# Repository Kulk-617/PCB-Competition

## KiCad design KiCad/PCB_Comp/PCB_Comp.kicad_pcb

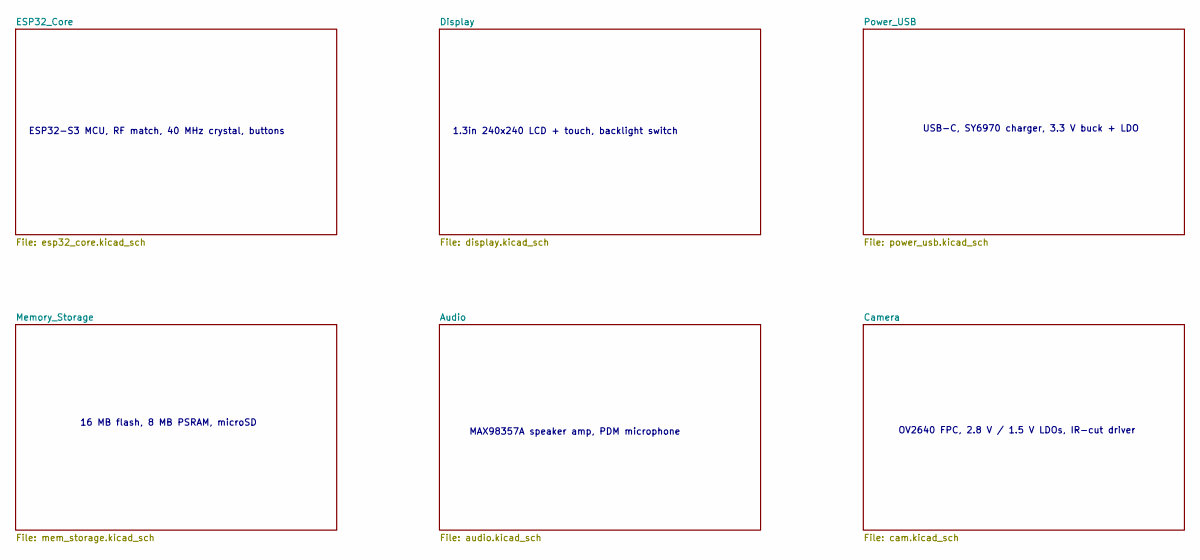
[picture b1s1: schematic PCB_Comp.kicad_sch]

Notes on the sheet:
ESP32-S3 MCU, RF match, 40 MHz crystal, buttons
16 MB flash, 8 MB PSRAM, microSD
OV2640 FPC, 2.8 V / 1.5 V LDOs, IR-cut driver
1.3in 240x240 LCD + touch, backlight switch
USB-C, SY6970 charger, 3.3 V buck + LDO
MAX98357A speaker amp, PDM microphone

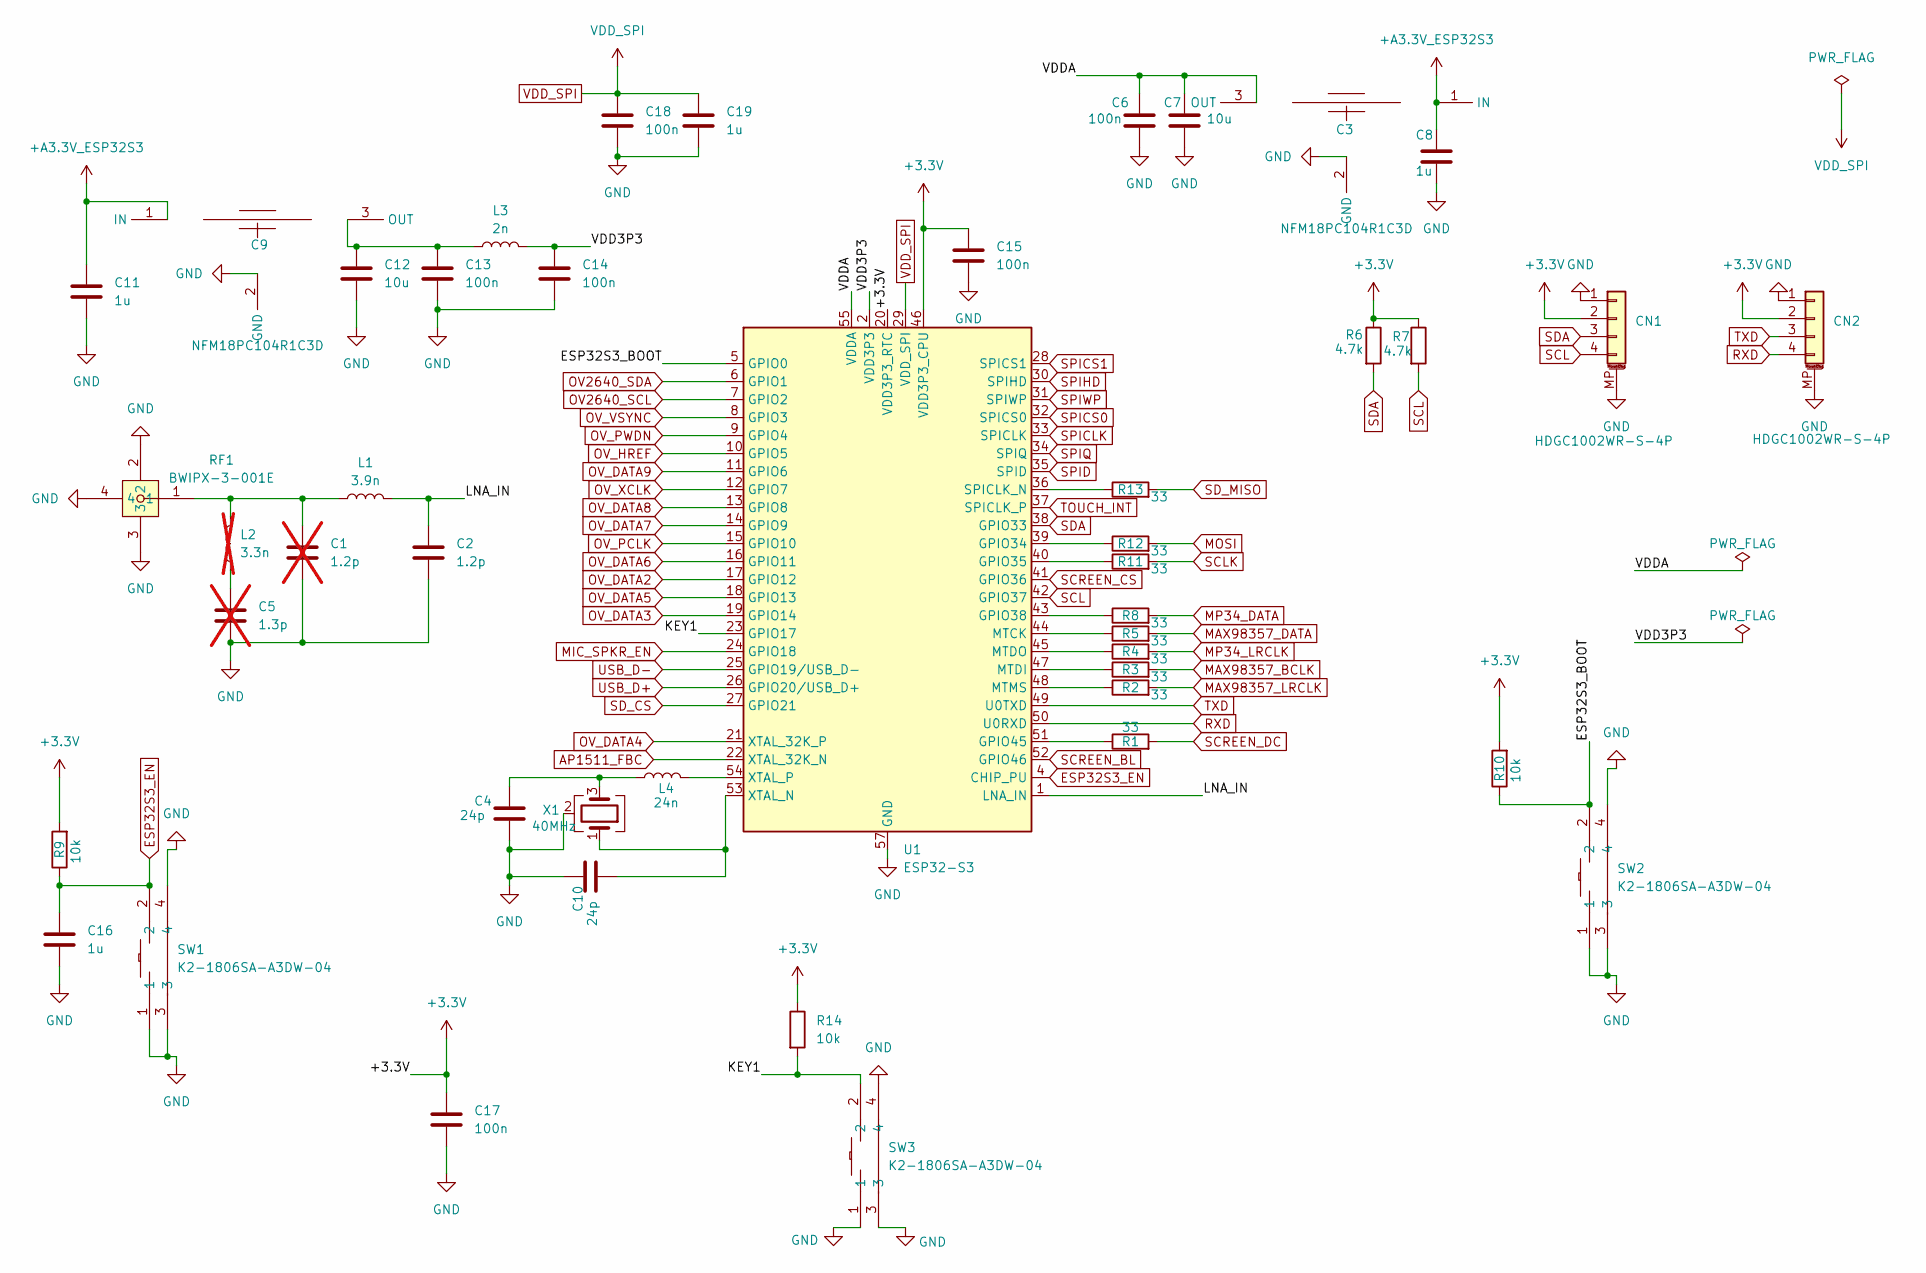
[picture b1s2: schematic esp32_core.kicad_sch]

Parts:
C1: 1.2p; C_0402_1005Metric; not fitted
C2: 1.2p; C_0402_1005Metric
C3, C9: NFM18PC104R1C3D; FILTER-SMD_3P-L1.6-W0.8-L_NFM18CC223R1C3D; MPN NFM18PC104R1C3D; LCSC Part C111493
C4, C10: 24p; C_0402_1005Metric
C5: 1.3p; C_0402_1005Metric; not fitted
C6, C13, C14, C15, C17, C18: 100n; C_0402_1005Metric
C7, C12: 10u; C_0603_1608Metric
C8, C11, C16, C19: 1u; C_0402_1005Metric
CN1, CN2: HDGC1002WR-S-4P; JST_SH_SM04B-SRSS-TB_1x04-1MP_P1.00mm_Horizontal
L1: 3.9n; L_0402_1005Metric
L2: 3.3n; L_0402_1005Metric; not fitted
L3: 2n; L_0402_1005Metric
L4: 24n; L_0402_1005Metric
R1, R2, R3, R4, R5, R8, R11, R12, R13: 33; R_0402_1005Metric
R6, R7: 4.7k; R_0402_1005Metric
R9, R10, R14: 10k; R_0402_1005Metric
RF1: BWIPX-3-001E; IPEX-SMD_BWIPX-3-001E-1; MPN BWIPX-3-001E; LCSC Part C784400
SW1, SW2, SW3: K2-1806SA-A3DW-04; KEY-SMD_K2-1806SA-AXXW-XX; MPN K2-1806SA-A3DW-04; LCSC Part C2690015
U1: ESP32-S3; QFN-56-1EP_7x7mm_P0.4mm_EP4x4mm
X1: 40MHz; Crystal_SMD_3225-4Pin_3.2x2.5mm

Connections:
+3.3V: C15.1, C17.1, CN1.2, CN2.2, R6.1, R7.1, R9.2, R10.2, R14.1, U1.20 (VDD3P3_RTC), U1.46 (VDD3P3_CPU); also elsewhere on the board
+A3.3V_ESP32S3: C3.1 (IN), C8.1, C9.1 (IN), C11.1; also elsewhere on the board
/ESP32_Core/ESP32S3_BOOT: R10.1, SW2.2, U1.5 (GPIO0)
/ESP32_Core/KEY1: R14.2, SW3.2, U1.23 (GPIO17)
/ESP32_Core/LNA_IN: C2.1, L1.2, U1.1 (LNA_IN)
/ESP32_Core/VDD3P3: C14.1, L3.2, U1.2 (VDD3P3), U1.3 (VDD3P3)
/ESP32_Core/VDDA: C3.3 (OUT), C6.1, C7.1, U1.55 (VDDA), U1.56 (VDDA)
AP1511_FBC: U1.22 (XTAL_32K_N); also elsewhere on the board
ESP32S3_EN: C16.1, R9.1, SW1.2, U1.4 (CHIP_PU)
GND: C1.2, C2.2, C3.2 (GND), C4.2, C5.2, C6.2, C7.2, C8.2, C9.2 (GND), C10.1, C11.2, C12.2, C13.2, C14.2, C15.2, C16.2, C17.2, C18.2, C19.2, CN1.1, CN1.MP (MountPin), CN2.1, CN2.MP (MountPin), RF1.2, RF1.3, RF1.4, SW1.1, SW1.3, SW1.4, SW2.1, SW2.3, SW2.4, SW3.1, SW3.3, SW3.4, U1.57 (GND), X1.2 (G), X1.4 (G); also elsewhere on the board
MAX98357_BCLK: R3.2; also elsewhere on the board
MAX98357_DATA: R5.2; also elsewhere on the board
MAX98357_LRCLK: R2.2; also elsewhere on the board
MIC_SPKR_EN: U1.24 (GPIO18); also elsewhere on the board
MOSI: R12.2; also elsewhere on the board
MP34_DATA: R8.2; also elsewhere on the board
MP34_LRCLK: R4.2; also elsewhere on the board
unnamed: C1.1, L1.1, L2.2, RF1.1
unnamed: C4.1, L4.1, X1.3
unnamed: C5.1, L2.1
unnamed: C9.3 (OUT), C12.1, C13.1, L3.1
unnamed: R12.1, U1.39 (GPIO34)
unnamed: R11.1, U1.40 (GPIO35)
unnamed: R8.1, U1.43 (GPIO38)
unnamed: R1.1, U1.51 (GPIO45)
unnamed: R5.1, U1.44 (MTCK)
unnamed: R3.1, U1.47 (MTDI)
unnamed: R4.1, U1.45 (MTDO)
unnamed: R2.1, U1.48 (MTMS)
unnamed: R13.1, U1.36 (SPICLK_N)
unnamed: C10.2, U1.53 (XTAL_N), X1.1
unnamed: L4.2, U1.54 (XTAL_P)
OV2640_SCL: U1.7 (GPIO2); also elsewhere on the board
OV2640_SDA: U1.6 (GPIO1); also elsewhere on the board
OV_DATA2: U1.17 (GPIO12); also elsewhere on the board
OV_DATA3: U1.19 (GPIO14); also elsewhere on the board
OV_DATA4: U1.21 (XTAL_32K_P); also elsewhere on the board
OV_DATA5: U1.18 (GPIO13); also elsewhere on the board
OV_DATA6: U1.16 (GPIO11); also elsewhere on the board
OV_DATA7: U1.14 (GPIO9); also elsewhere on the board
OV_DATA8: U1.13 (GPIO8); also elsewhere on the board
OV_DATA9: U1.11 (GPIO6); also elsewhere on the board
OV_HREF: U1.10 (GPIO5); also elsewhere on the board
OV_PCLK: U1.15 (GPIO10); also elsewhere on the board
OV_PWDN: U1.9 (GPIO4); also elsewhere on the board
OV_VSYNC: U1.8 (GPIO3); also elsewhere on the board
OV_XCLK: U1.12 (GPIO7); also elsewhere on the board
RXD: CN2.4, U1.50 (U0RXD)
SCL: CN1.4, R7.2, U1.42 (GPIO37); also elsewhere on the board
SCLK: R11.2; also elsewhere on the board
SCREEN_BL: U1.52 (GPIO46); also elsewhere on the board
SCREEN_CS: U1.41 (GPIO36); also elsewhere on the board
SCREEN_DC: R1.2; also elsewhere on the board
SDA: CN1.3, R6.2, U1.38 (GPIO33); also elsewhere on the board
SD_CS: U1.27 (GPIO21); also elsewhere on the board
SD_MISO: R13.2; also elsewhere on the board
SPICLK: U1.33 (SPICLK); also elsewhere on the board
SPICS0: U1.32 (SPICS0); also elsewhere on the board
SPICS1: U1.28 (SPICS1); also elsewhere on the board
SPID: U1.35 (SPID); also elsewhere on the board
SPIHD: U1.30 (SPIHD); also elsewhere on the board
SPIQ: U1.34 (SPIQ); also elsewhere on the board
SPIWP: U1.31 (SPIWP); also elsewhere on the board
TOUCH_INT: U1.37 (SPICLK_P); also elsewhere on the board
TXD: CN2.3, U1.49 (U0TXD)
USB_D+: U1.26 (GPIO20/USB_D+); also elsewhere on the board
USB_D-: U1.25 (GPIO19/USB_D-); also elsewhere on the board
VDD_SPI: C18.1, C19.1, U1.29 (VDD_SPI); also elsewhere on the board

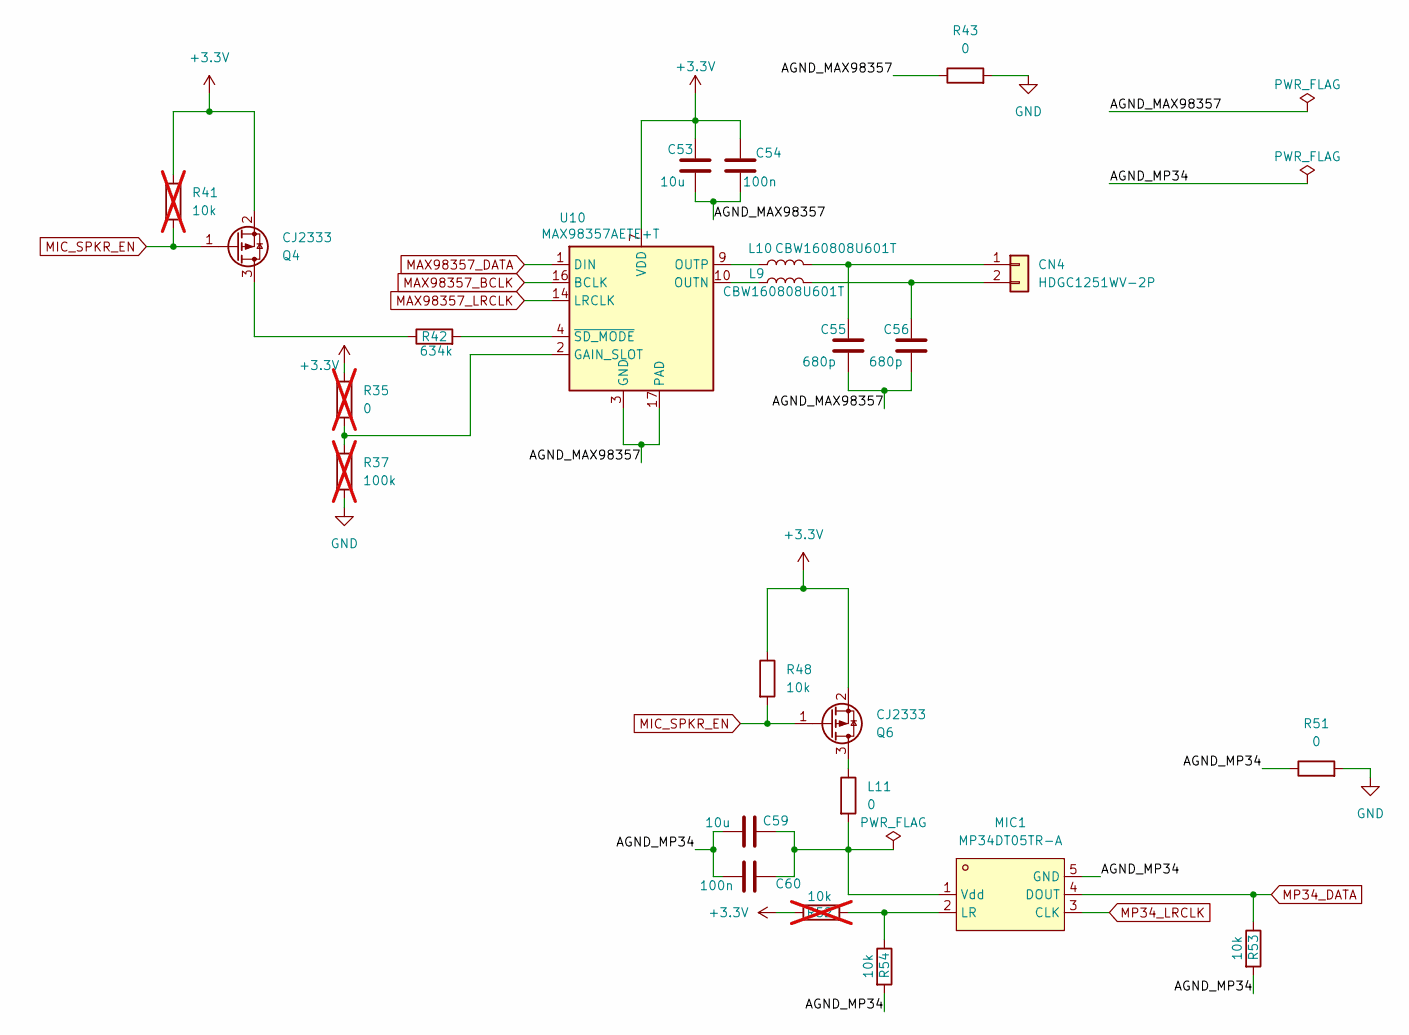
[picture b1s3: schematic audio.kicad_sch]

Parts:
C53, C59: 10u; C_0603_1608Metric
C54, C60: 100n; C_0402_1005Metric
C55, C56: 680p; C_0402_1005Metric
CN4: HDGC1251WV-2P; CONN-TH_2P-P1.25_HDGC1251WV-2P
L9, L10: CBW160808U601T; L_0603_1608Metric
L11: 0; R_0402_1005Metric
MIC1: MP34DT05TR-A; MIC-SMD_5P-L3.0-W4.0-P0.85-BL; MPN MP34DT05TR-A; LCSC Part C2688664
Q4, Q6: CJ2333; SOT-23
R35: 0; R_0402_1005Metric; not fitted
R37: 100k; R_0402_1005Metric; not fitted
R41, R52: 10k; R_0402_1005Metric; not fitted
R42: 634k; R_0402_1005Metric
R43, R51: 0; R_0603_1608Metric
R48, R53, R54: 10k; R_0402_1005Metric
U10: MAX98357AETE+T; TQFN-16-1EP_3x3mm_P0.5mm_EP1.23x1.23mm

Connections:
+3.3V: C53.1, C54.1, Q4.2 (S), Q6.2 (S), R35.1, R41.1, R48.1, R52.1, U10.7 (VDD), U10.8 (VDD); also elsewhere on the board
/Audio/AGND_MAX98357: C53.2, C54.2, C55.2, C56.2, R43.1, U10.3 (GND), U10.11 (GND), U10.15 (GND), U10.17 (PAD)
/Audio/AGND_MP34: C59.2, C60.2, MIC1.5 (GND), R51.1, R53.2, R54.2
GND: R37.2, R43.2, R51.2; also elsewhere on the board
MAX98357_BCLK: U10.16 (BCLK); also elsewhere on the board
MAX98357_DATA: U10.1 (DIN); also elsewhere on the board
MAX98357_LRCLK: U10.14 (LRCLK); also elsewhere on the board
MIC_SPKR_EN: Q4.1 (G), Q6.1 (G), R41.2, R48.2; also elsewhere on the board
MP34_DATA: MIC1.4 (DOUT), R53.1; also elsewhere on the board
MP34_LRCLK: MIC1.3 (CLK); also elsewhere on the board
unnamed: C55.1, CN4.1, L10.2
unnamed: C56.1, CN4.2, L9.2
unnamed: MIC1.2 (LR), R52.2, R54.1
unnamed: C59.1, C60.1, L11.2, MIC1.1 (Vdd)
unnamed: Q4.3 (D), R42.1
unnamed: L11.1, Q6.3 (D)
unnamed: R35.2, R37.1, U10.2 (GAIN_SLOT)
unnamed: L9.1, U10.10 (OUTN)
unnamed: L10.1, U10.9 (OUTP)
unnamed: R42.2, U10.4 (~SD_MODE)

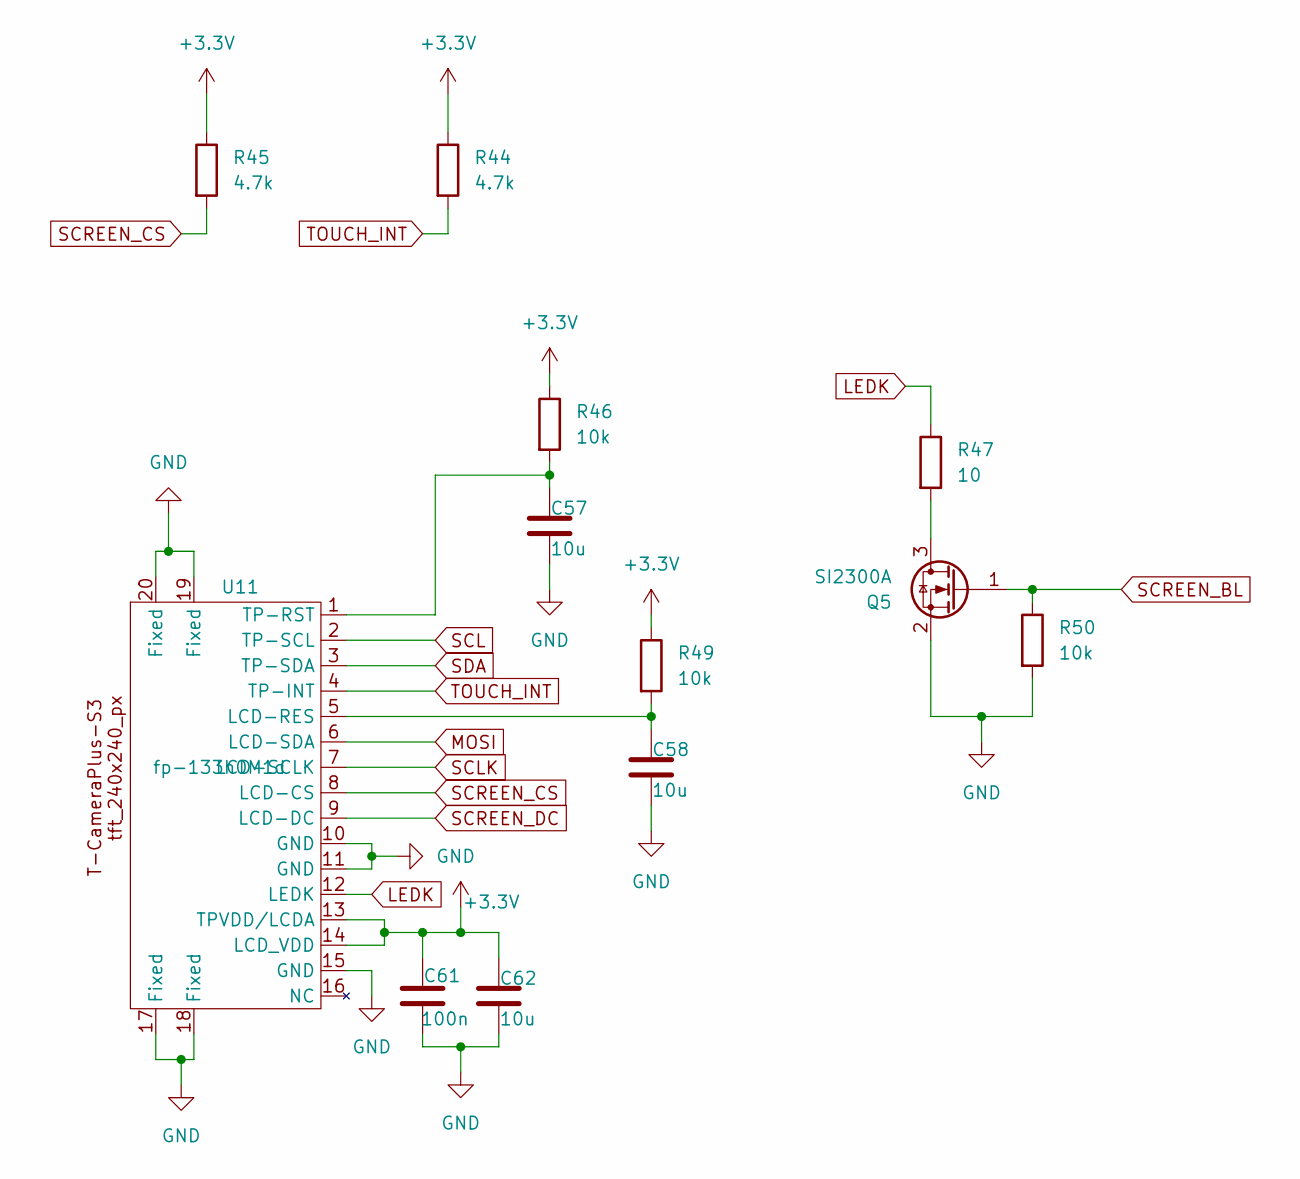
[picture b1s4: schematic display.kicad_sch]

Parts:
C57, C58, C62: 10u; C_0603_1608Metric
C61: 100n; C_0402_1005Metric
Q5: SI2300A; SOT-23
R44, R45: 4.7k; R_0402_1005Metric
R46, R49, R50: 10k; R_0402_1005Metric
R47: 10; R_0402_1005Metric
U11: fp-133h0M1d; LCD_FPC-16P_P0.5mm_FH12-16S

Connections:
+3.3V: C61.1, C62.1, R44.1, R45.1, R46.1, R49.1, U11.13 (TPVDD/LCDA), U11.14 (LCD_VDD); also elsewhere on the board
GND: C57.2, C58.2, C61.2, C62.2, Q5.2 (S), R50.2, U11.10 (GND), U11.11 (GND), U11.15 (GND), U11.17 (Fixed), U11.18 (Fixed), U11.19 (Fixed), U11.20 (Fixed); also elsewhere on the board
LEDK: R47.1, U11.12 (LEDK)
MOSI: U11.6 (LCD-SDA); also elsewhere on the board
unnamed: Q5.3 (D), R47.2
unnamed: C58.1, R49.2, U11.5 (LCD-RES)
unnamed: C57.1, R46.2, U11.1 (TP-RST)
SCL: U11.2 (TP-SCL); also elsewhere on the board
SCLK: U11.7 (LCD-SCLK); also elsewhere on the board
SCREEN_BL: Q5.1 (G), R50.1; also elsewhere on the board
SCREEN_CS: R45.2, U11.8 (LCD-CS); also elsewhere on the board
SCREEN_DC: U11.9 (LCD-DC); also elsewhere on the board
SDA: U11.3 (TP-SDA); also elsewhere on the board
TOUCH_INT: R44.2, U11.4 (TP-INT); also elsewhere on the board

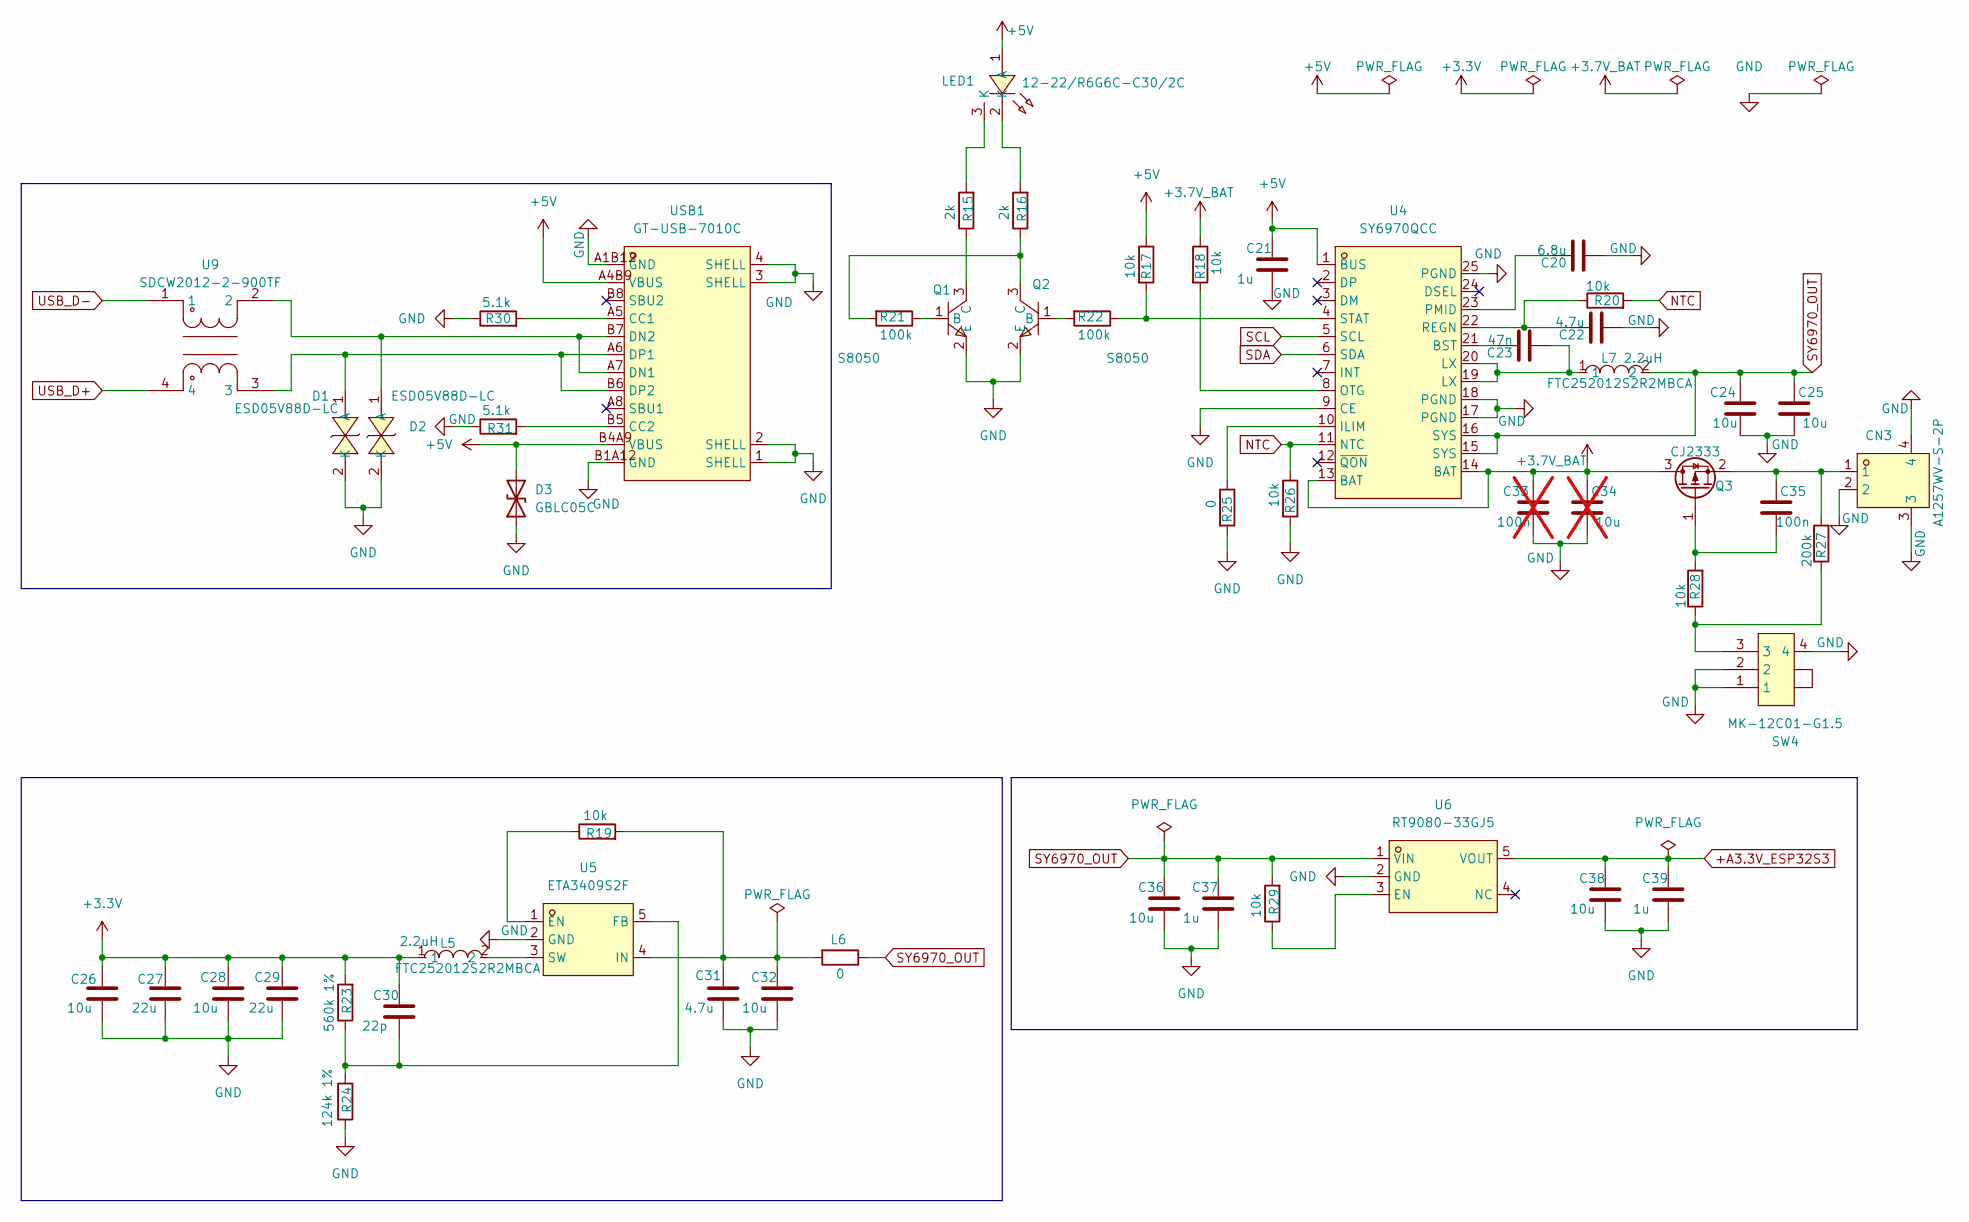
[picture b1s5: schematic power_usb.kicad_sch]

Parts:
C20: 6.8u; C_0603_1608Metric
C21, C37, C39: 1u; C_0402_1005Metric
C22, C31: 4.7u; C_0603_1608Metric
C23: 47n; C_0402_1005Metric
C24, C25, C26, C28, C32, C36, C38: 10u; C_0603_1608Metric
C27, C29: 22u; C_0805_2012Metric
C30: 22p; C_0402_1005Metric
C33: 100n; C_0402_1005Metric; not fitted
C34: 10u; C_0603_1608Metric; not fitted
C35: 100n; C_0402_1005Metric
CN3: A1257WV-S-2P; CONN-SMD_A1257WV-S-2P; MPN A1257WV-S-2P-LCP; LCSC Part C225118
D1, D2: ESD05V88D-LC; DFN1006-2L-BI; MPN ESD05V88D-LC; LCSC Part C5139330
D3: GBLC05C; D_SOD-323
L5, L7: 2.2uH; IND-SMD_L2.5-W2.0_MHCHL2520; MPN FTC252012S2R2MBCA; LCSC Part C5832372
L6: 0; R_0805_2012Metric
LED1: 12-22/R6G6C-C30/2C; LED-SMD_R6G6C-C30; MPN 12-22/R6G6C-C30/2C; LCSC Part C970147
Q1, Q2: S8050; SOT-23-3_L2.9-W1.3-P1.90-LS2.4-BR; MPN S8050; LCSC Part C2891804
Q3: CJ2333; SOT-23
R15, R16: 2k; R_0402_1005Metric
R17, R18, R19, R20, R26, R28, R29: 10k; R_0402_1005Metric
R21, R22: 100k; R_0402_1005Metric
R23: 560k 1%; R_0402_1005Metric
R24: 124k 1%; R_0402_1005Metric
R25: 0; R_0402_1005Metric
R27: 200k; R_0402_1005Metric
R30, R31: 5.1k; R_0402_1005Metric
SW4: MK-12C01-G1.5; SW-SMD_DEALON_MK-12C01-G1.5; MPN MK-12C01-G1.5; LCSC Part C2904924
U4: SY6970QCC; QFN-24_L4.0-W4.0-P0.50-TL-EP2.7; MPN SY6970QCC; LCSC Part C5357542
U5: ETA3409S2F; SOT-23-5_L2.9-W1.6-P0.95-LS2.8-BL; MPN ETA3409S2F; LCSC Part C7465553
U6: RT9080-33GJ5; TSOT-23-5_L2.9-W1.6-P0.95-LS2.8-BL; MPN RT9080-33GJ5; LCSC Part C841192
U9: SDCW2012-2-900TF; FILTER-SMD_4P-L2.0-W1.3-BL_DLW21; MPN SDCW2012-2-900TF; LCSC Part C54888
USB1: GT-USB-7010C; USB-C-SMD_GT-USB-7010C; MPN GT-USB-7010C; LCSC Part C2843967

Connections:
+3.3V: C26.1, C27.1, C28.1, C29.1, C30.1, L5.1, R23.2; also elsewhere on the board
+3.7V_BAT: C33.2, C34.2, Q3.3 (D), R18.1, U4.13 (BAT), U4.14 (BAT)
+5V: C21.1, D3.2 (A2), LED1.1 (A), R17.1, U4.1 (BUS), USB1.A4B9 (VBUS), USB1.B4A9 (VBUS)
+A3.3V_ESP32S3: C38.1, C39.1, U6.5 (VOUT); also elsewhere on the board
GND: C20.2, C21.2, C22.2, C24.1, C25.1, C26.2, C27.2, C28.2, C29.2, C31.2, C32.2, C33.1, C34.1, C36.2, C37.2, C38.2, C39.2, CN3.2, CN3.3, CN3.4, D1.2 (K), D2.2 (K), D3.1 (A1), Q1.2 (E), Q2.2 (E), R24.1, R25.2, R26.2, R30.1, R31.1, SW4.1, SW4.2, SW4.4, U4.9 (CE), U4.17 (PGND), U4.18 (PGND), U4.25 (PGND), U5.2 (GND), U6.2 (GND), USB1.1 (SHELL), USB1.2 (SHELL), USB1.3 (SHELL), USB1.4 (SHELL), USB1.A1B12 (GND), USB1.B1A12 (GND); also elsewhere on the board
NTC: R20.2, R26.1, U4.11 (NTC)
unnamed: C23.2, L7.1, U4.19 (LX), U4.20 (LX)
unnamed: D1.1 (A), U9.3, USB1.A6 (DP1), USB1.B6 (DP2)
unnamed: D2.1 (A), U9.2, USB1.A7 (DN1), USB1.B7 (DN2)
unnamed: LED1.2 (K), R16.2
unnamed: LED1.3 (K), R15.2
unnamed: Q1.1 (B), R21.1
unnamed: Q1.3 (C), R15.1
unnamed: Q2.1 (B), R22.2
unnamed: Q2.3 (C), R16.1, R21.2
unnamed: C35.1, Q3.1 (G), R28.2
unnamed: C35.2, CN3.1, Q3.2 (S), R27.2
unnamed: R27.1, R28.1, SW4.3
unnamed: C23.1, U4.21 (BST)
unnamed: R25.1, U4.10 (ILIM)
unnamed: R18.2, U4.8 (OTG)
unnamed: C20.1, U4.23 (PMID)
unnamed: C22.1, R20.1, U4.22 (REGN)
unnamed: R17.2, R22.1, U4.4 (STAT)
unnamed: R19.1, U5.1 (EN)
unnamed: C30.2, R23.1, R24.2, U5.5 (FB)
unnamed: C31.1, C32.1, L6.2, R19.2, U5.4 (IN)
unnamed: L5.2, U5.3 (SW)
unnamed: R29.1, U6.3 (EN)
unnamed: R30.2, USB1.A5 (CC1)
unnamed: R31.2, USB1.B5 (CC2)
SCL: U4.5 (SCL); also elsewhere on the board
SDA: U4.6 (SDA); also elsewhere on the board
SY6970_OUT: C24.2, C25.2, C36.1, C37.1, L6.1, L7.2, R29.2, U4.15 (SYS), U4.16 (SYS), U6.1 (VIN); also elsewhere on the board
USB_D+: U9.4; also elsewhere on the board
USB_D-: U9.1; also elsewhere on the board

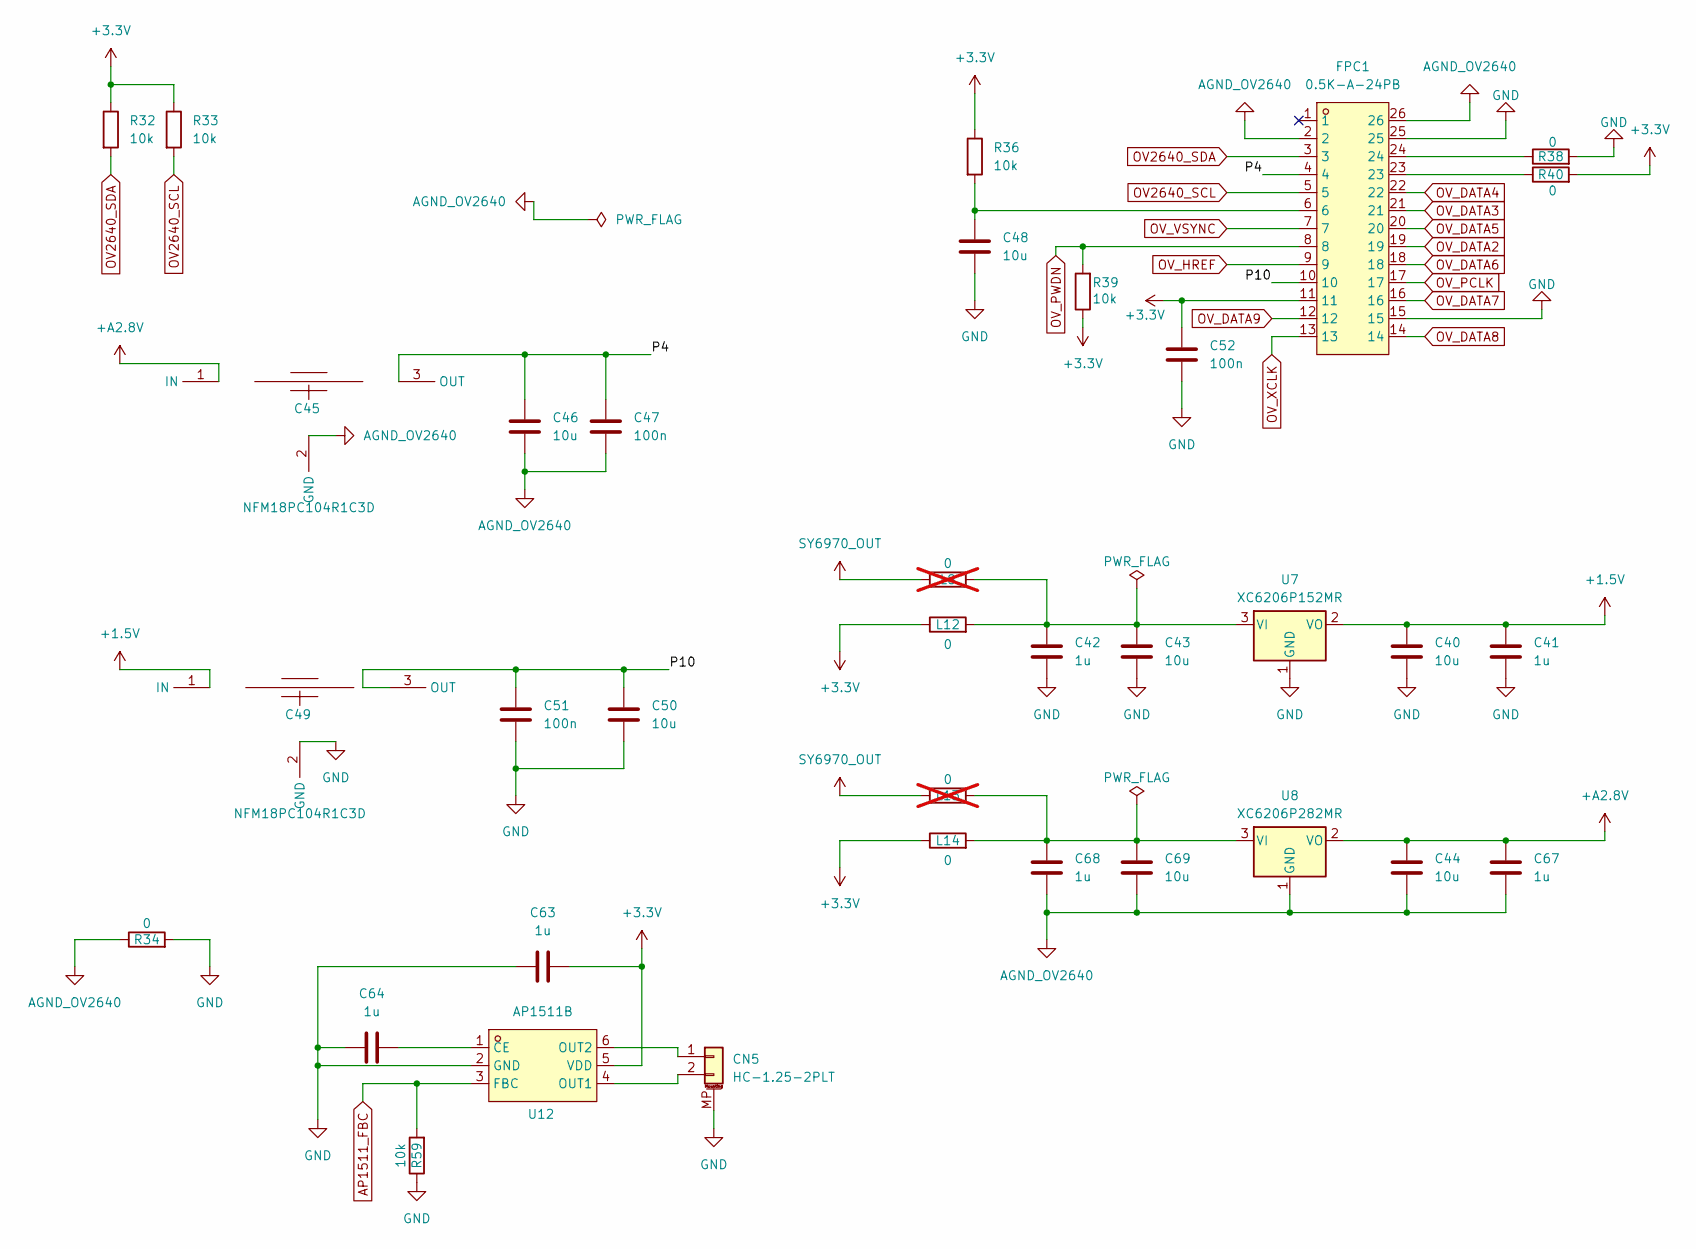
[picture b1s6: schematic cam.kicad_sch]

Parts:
C40, C43, C44, C46, C48, C50, C69: 10u; C_0603_1608Metric
C41, C42, C63, C64, C67, C68: 1u; C_0402_1005Metric
C45, C49: NFM18PC104R1C3D; FILTER-SMD_3P-L1.6-W0.8-L_NFM18CC223R1C3D; MPN NFM18PC104R1C3D; LCSC Part C111493
C47, C51, C52: 100n; C_0402_1005Metric
CN5: HC-1.25-2PLT; Molex_PicoBlade_53261-0271_1x02-1MP_P1.25mm_Horizontal
FPC1: 0.5K-A-24PB; CONN-SMD_0.5K-A-24PB; MPN 0.5K-A-24PB; LCSC Part C2914148
L8, L13: 0; R_0402_1005Metric; not fitted
L12, L14: 0; R_0402_1005Metric
R32, R33, R36, R39, R59: 10k; R_0402_1005Metric
R34: 0; R_0603_1608Metric
R38, R40: 0; R_0402_1005Metric
U7: XC6206P152MR; SOT-23-3
U8: XC6206P282MR; SOT-23-3
U12: AP1511B; SOT-23-6_L2.9-W1.6-P0.95-LS2.9-BL; MPN AP1511B; LCSC Part C22358680

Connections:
+1.5V: C40.1, C41.1, C49.1 (IN), U7.2 (VO)
+3.3V: C52.1, C63.2, FPC1.11, L12.1, L14.1, R32.1, R33.1, R36.1, R39.1, R40.2, U12.5 (VDD); also elsewhere on the board
+A2.8V: C44.1, C45.1 (IN), C67.1, U8.2 (VO); also elsewhere on the board
/Camera/P4: C45.3 (OUT), C46.1, C47.1, FPC1.4
/Camera/P10: C49.3 (OUT), C50.1, C51.1, FPC1.10
AGND_OV2640: C44.2, C45.2 (GND), C46.2, C47.2, C67.2, C68.2, C69.2, FPC1.2, FPC1.26, R34.1, U8.1 (GND); also elsewhere on the board
AP1511_FBC: R59.2, U12.3 (FBC); also elsewhere on the board
GND: C40.2, C41.2, C42.2, C43.2, C48.2, C49.2 (GND), C50.2, C51.2, C52.2, C63.1, C64.1, CN5.MP (MountPin), FPC1.15, FPC1.25, R34.2, R38.2, R59.1, U7.1 (GND), U12.2 (GND); also elsewhere on the board
unnamed: C48.1, FPC1.6, R36.2
unnamed: CN5.1, U12.6 (OUT2)
unnamed: CN5.2, U12.4 (OUT1)
unnamed: FPC1.23, R40.1
unnamed: FPC1.24, R38.1
unnamed: C42.1, C43.1, L8.2, L12.2, U7.3 (VI)
unnamed 79: C68.1, C69.1, L13.2, L14.2, U8.3 (VI); also elsewhere on the board
unnamed: C64.2, U12.1 (CE)
OV2640_SCL: FPC1.5, R33.2; also elsewhere on the board
OV2640_SDA: FPC1.3, R32.2; also elsewhere on the board
OV_DATA2: FPC1.19; also elsewhere on the board
OV_DATA3: FPC1.21; also elsewhere on the board
OV_DATA4: FPC1.22; also elsewhere on the board
OV_DATA5: FPC1.20; also elsewhere on the board
OV_DATA6: FPC1.18; also elsewhere on the board
OV_DATA7: FPC1.16; also elsewhere on the board
OV_DATA8: FPC1.14; also elsewhere on the board
OV_DATA9: FPC1.12; also elsewhere on the board
OV_HREF: FPC1.9; also elsewhere on the board
OV_PCLK: FPC1.17; also elsewhere on the board
OV_PWDN: FPC1.8, R39.2; also elsewhere on the board
OV_VSYNC: FPC1.7; also elsewhere on the board
OV_XCLK: FPC1.13; also elsewhere on the board
SY6970_OUT: L8.1, L13.1; also elsewhere on the board

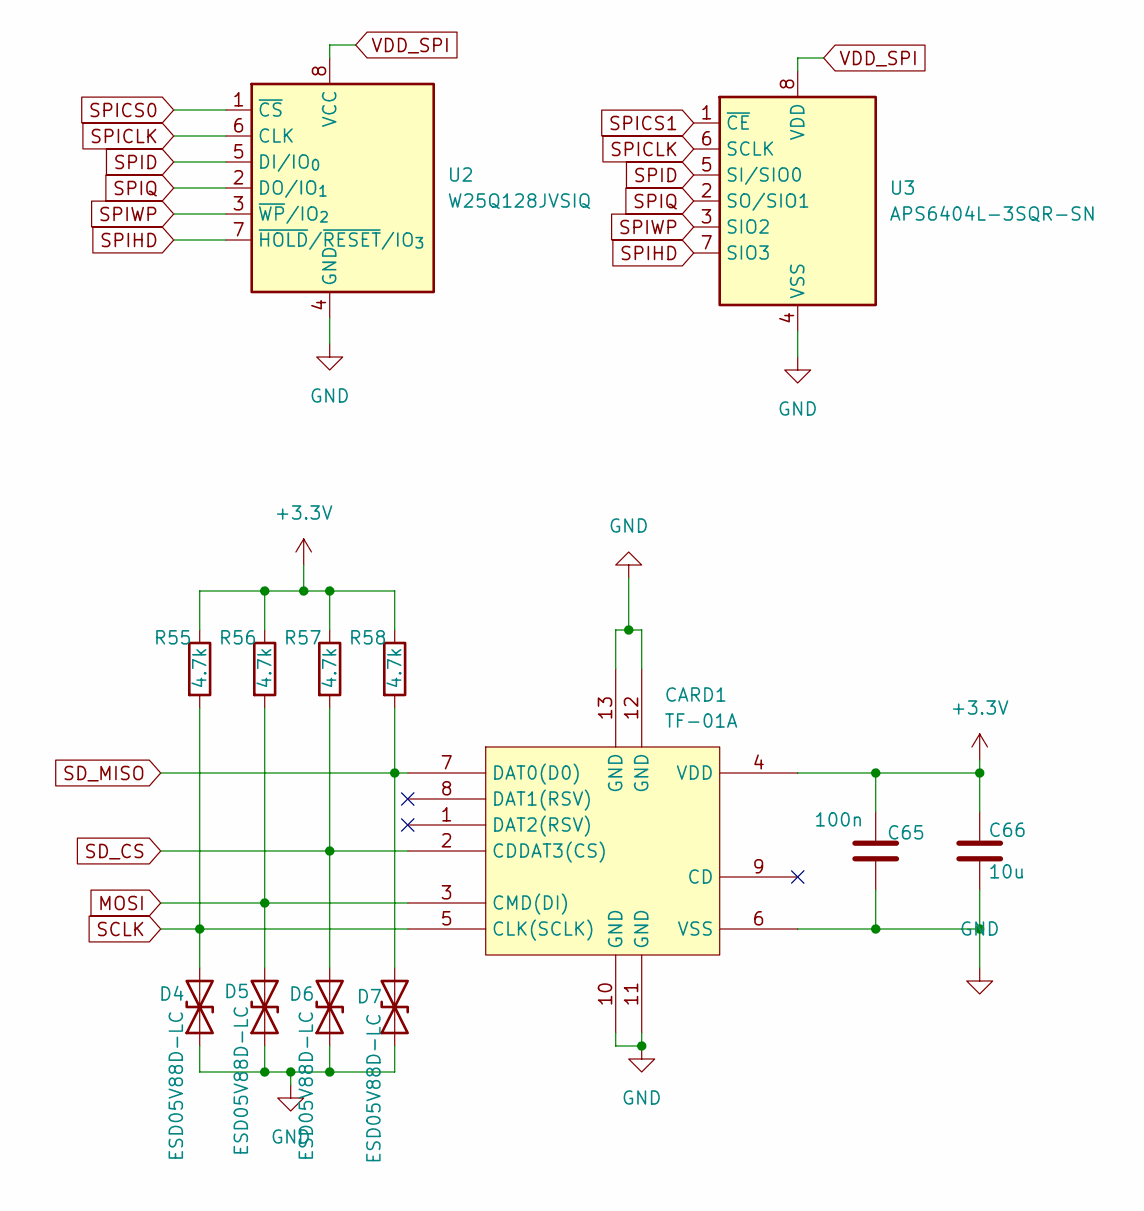
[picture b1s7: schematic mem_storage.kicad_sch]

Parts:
C65: 100n; C_0402_1005Metric
C66: 10u; C_0603_1608Metric
CARD1: TF-01A; TF-SMD_TF-01A; MPN TF-01A; LCSC Part C91145
D4, D5, D6, D7: ESD05V88D-LC; DFN1006-2L-BI
R55, R56, R57, R58: 4.7k; R_0402_1005Metric
U2: W25Q128JVSIQ; SOIC-8_5.3x5.3mm_P1.27mm
U3: APS6404L-3SQR-SN; SOIC-8_3.9x4.9mm_P1.27mm

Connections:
+3.3V: C65.1, C66.1, CARD1.4 (VDD), R55.1, R56.1, R57.1, R58.1; also elsewhere on the board
GND: C65.2, C66.2, CARD1.6 (VSS), CARD1.10 (GND), CARD1.11 (GND), CARD1.12 (GND), CARD1.13 (GND), D4.1 (A1), D5.1 (A1), D6.1 (A1), D7.1 (A1), U2.4 (GND), U3.4 (VSS); also elsewhere on the board
MOSI: CARD1.3 (CMD(DI)), D5.2 (A2), R56.2; also elsewhere on the board
SCLK: CARD1.5 (CLK(SCLK)), D4.2 (A2), R55.2; also elsewhere on the board
SD_CS: CARD1.2 (CDDAT3(CS)), D6.2 (A2), R57.2; also elsewhere on the board
SD_MISO: CARD1.7 (DAT0(D0)), D7.2 (A2), R58.2; also elsewhere on the board
SPICLK: U2.6 (CLK), U3.6 (SCLK); also elsewhere on the board
SPICS0: U2.1 (~CS); also elsewhere on the board
SPICS1: U3.1 (~CE); also elsewhere on the board
SPID: U2.5 (DI/IO_{0}), U3.5 (SI/SIO0); also elsewhere on the board
SPIHD: U2.7 (~HOLD/~RESET/IO_{3}), U3.7 (SIO3); also elsewhere on the board
SPIQ: U2.2 (DO/IO_{1}), U3.2 (SO/SIO1); also elsewhere on the board
SPIWP: U2.3 (~WP/IO_{2}), U3.3 (SIO2); also elsewhere on the board
VDD_SPI: U2.8 (VCC), U3.8 (VDD); also elsewhere on the board

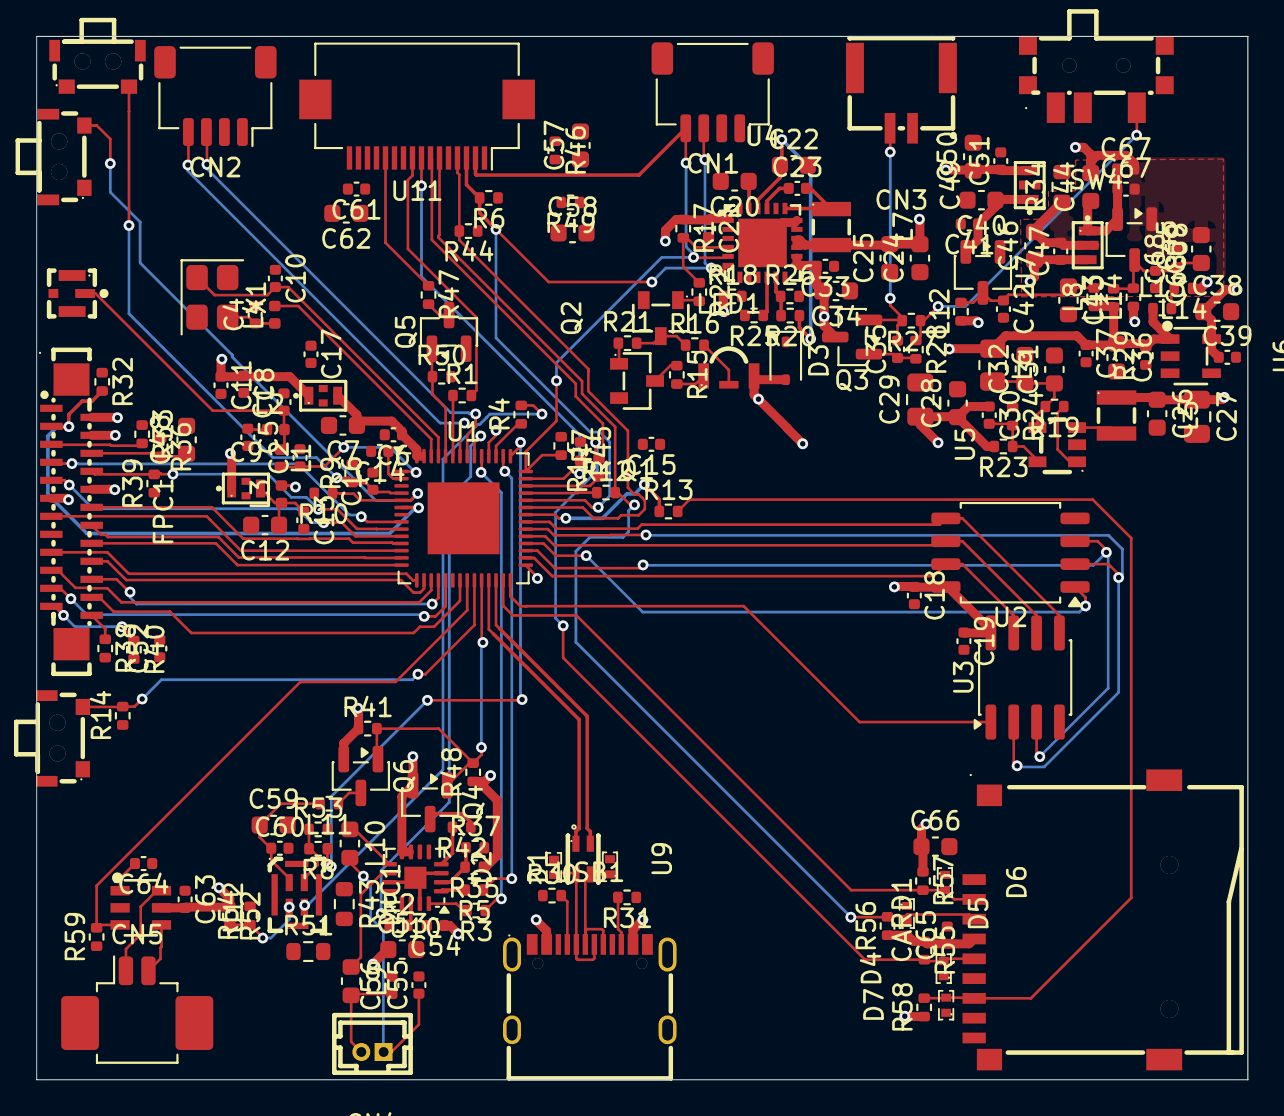
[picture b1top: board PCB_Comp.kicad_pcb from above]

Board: 4 copper layers, 67.3 x 58.0 mm, 187 parts (0 on the bottom side), 126 nets.

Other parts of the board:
C67#2, C68#2: 1u; C_0402_1005Metric
L13#2, L14#2: 0; R_0402_1005Metric

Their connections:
+3.3V: L14#2.1; also elsewhere on the board
+A2.8V: C67#2.1; also elsewhere on the board
AGND_OV2640: C67#2.2, C68#2.2; also elsewhere on the board
unnamed 79: C68#2.1, L13#2.2, L14#2.2; also elsewhere on the board
SY6970_OUT: L13#2.1; also elsewhere on the board
